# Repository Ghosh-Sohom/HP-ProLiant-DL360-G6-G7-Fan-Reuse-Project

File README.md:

# HP Proliant DL360 G6/G7 Server Fan Assembly Module Reuse Project

This GitHub repository provides information, diagrams, PCB designs, and Arduino code to help users reuse the HP Proliant Series DL360 G6 and G7 fans. These fans come with proprietary connectors, which make them unusable outside their intended use. With the information and tools provided in this repository, users can now utilize these fans for other purposes, including computer cooling systems, personal projects, or other industrial applications.

## Table of Contents
- Overview
- Features
- Installation
- Usage
- Contributing
### Overview
The HP Proliant Series DL360 G6 and G7 fans are high-quality, durable, and efficient cooling solutions that have been used in various industrial applications. Unfortunately, their proprietary connectors make them difficult to use for other purposes, limiting their reuse outside their intended use.

This repository provides a comprehensive guide to enable users to repurpose these fans. We provide detailed information, diagrams, PCB designs, and Arduino code to help users get started with using these fans. Our goal is to ensure that these fans are not only reusable but also useful in other applications.

### Features
This repository includes the following features:

1. [Pinout diagram](https://in.pinterest.com/pin/29343835065663880/) for the proprietary connectors used in the HP Proliant Series DL360 G6 and G7 fans.
2. [PCB designs](https://github.com/Ghosh-Sohom/HP-ProLiant-DL360-G6-G7-Fan-Reuse-Project/blob/fa99ac65fb46d815a2f2a44f4c6c5ac0088795ca/HP%20DL360%20Fan%20PCB.kicad_pcb) for connecting the proprietary connectors to standard connectors.
3. [Arduino code](https://github.com/Ghosh-Sohom/HP-ProLiant-DL360-G6-G7-Fan-Reuse-Project/blob/fa99ac65fb46d815a2f2a44f4c6c5ac0088795ca/PWM_fan_control_code.ino) for controlling the fan speed using PWM.
4. Detailed information on how to repurpose the fans for different applications.
### Installation
To use this repository, simply clone or download the repository onto your local machine. You will need the following tools:

- Arduino IDE
- PCB design software
- Soldering equipment
### Usage
To use the HP Proliant Series DL360 G6 and G7 fans, follow these steps:

1. Use the pinout diagrams to identify the connections on the proprietary connectors.
2. Use the PCB designs to create a custom PCB that connects the proprietary connectors to standard connectors.
3. Solder the standard connectors onto the PCB.
4. Connect the fans to the standard connectors.
5. Use the Arduino code to control the fan speed using PWM.
For more detailed information on how to use these fans, please refer to the documentation provided in this repository.

### Contributing
We welcome contributions to this repository. If you have any suggestions or improvements, please feel free to submit a pull request. We also encourage you to submit issues if you encounter any problems or have questions about the repository.

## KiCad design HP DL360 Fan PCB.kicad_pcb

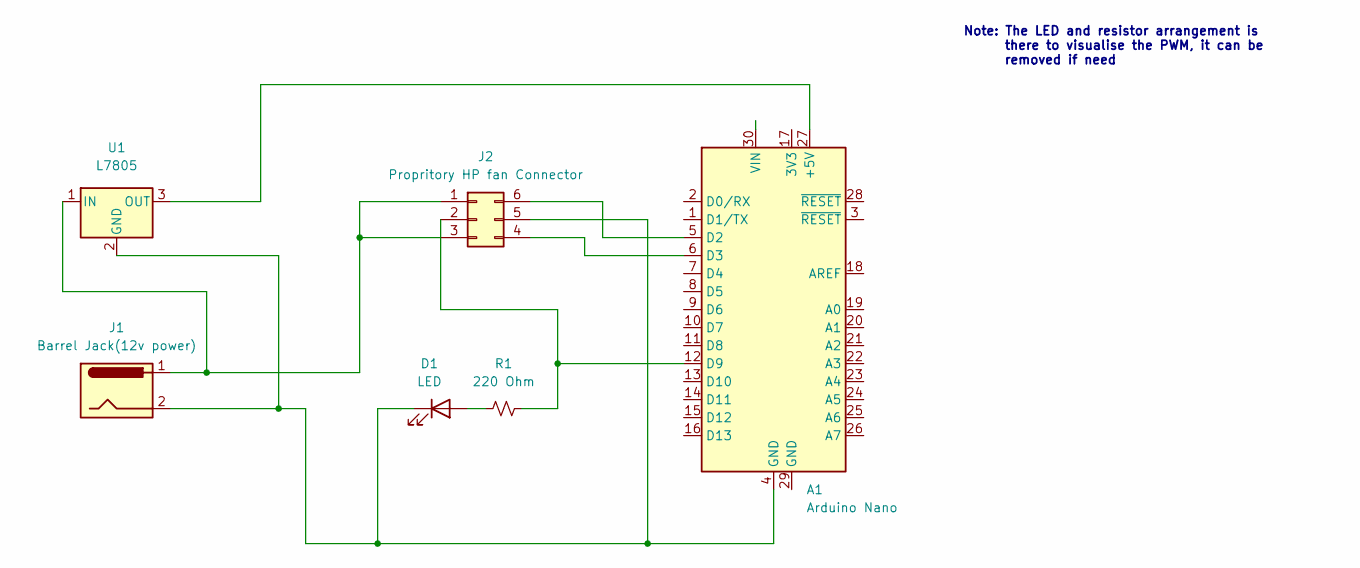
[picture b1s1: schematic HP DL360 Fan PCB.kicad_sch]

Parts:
A1: Arduino Nano; Arduino_Nano
D1: LED; LED_D2.0mm_W4.8mm_H2.5mm_FlatTop
J1: Barrel Jack(12v power); BarrelJack_Horizontal
J2: Propritory HP fan Connector; PinHeader_2x03_P1.00mm_Vertical
R1: 220 Ohm; R_Axial_DIN0204_L3.6mm_D1.6mm_P5.08mm_Horizontal
U1: L7805; TO-220-3_Vertical

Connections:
unnamed: A1.12 (D9), J2.2, R1.1
unnamed: A1.4 (GND), D1.1 (K), J1.2, J2.5, U1.2 (GND)
unnamed: J1.1, J2.1, J2.3, U1.1 (IN)
unnamed: A1.6 (D3), J2.4
unnamed: A1.5 (D2), J2.6
unnamed: D1.2 (A), R1.2
unnamed: A1.27 (+5V), U1.3 (OUT)

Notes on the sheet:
Note: The LED and resistor arrangement is there to visualise the PWM, it can be removed if need

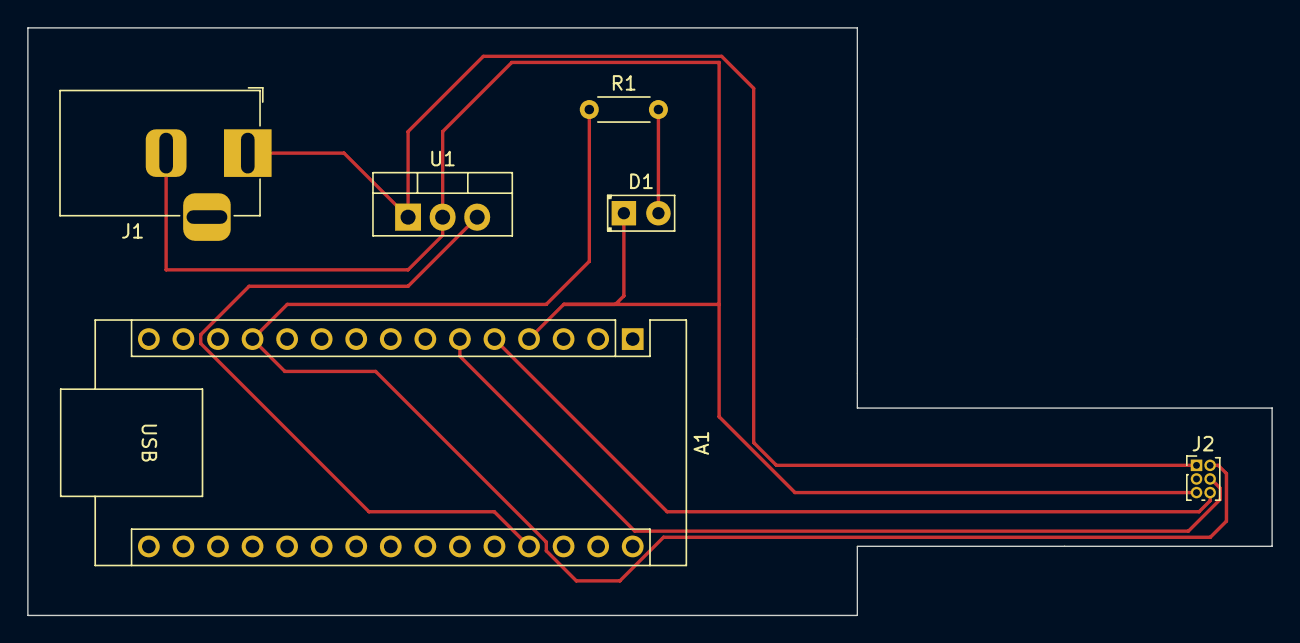
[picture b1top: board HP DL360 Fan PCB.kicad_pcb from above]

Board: 2 copper layers, 91.4 x 43.2 mm, 6 parts (0 on the bottom side), 7 nets.
